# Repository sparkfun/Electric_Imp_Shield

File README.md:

Electric Imp Shield
===================

[
*Electric Imp Shield (DEV-12887)*](https://www.sparkfun.com/products/12887)

The Electric Imp shield allows you to connect your Arduino to the Imp Cloud Service and connect to HTTP APIs. 

Repository Contents
-------------------
* **/Hardware** - All Eagle design files (.brd, .sch)
* **/Production** - Test bed files and production panel files

Product Versions
----------------
* [DEV-11401](https://www.sparkfun.com/products/retired/11401)- Version 1.1. Designed for Uno (not R3). Retired. 

Version History
---------------
* [v1.1](https://github.com/sparkfun/Electric_Imp_Shield/tree/V_1.1) Version 1.1

License Information
-------------------
The hardware is released under [Creative Commons ShareAlike 4.0 International](https://creativecommons.org/licenses/by-sa/4.0/).The code is beerware; if you see me (or any other SparkFun employee) at the local, and you've found our code helpful, please buy us a round!

Distributed as-is; no warranty is given.

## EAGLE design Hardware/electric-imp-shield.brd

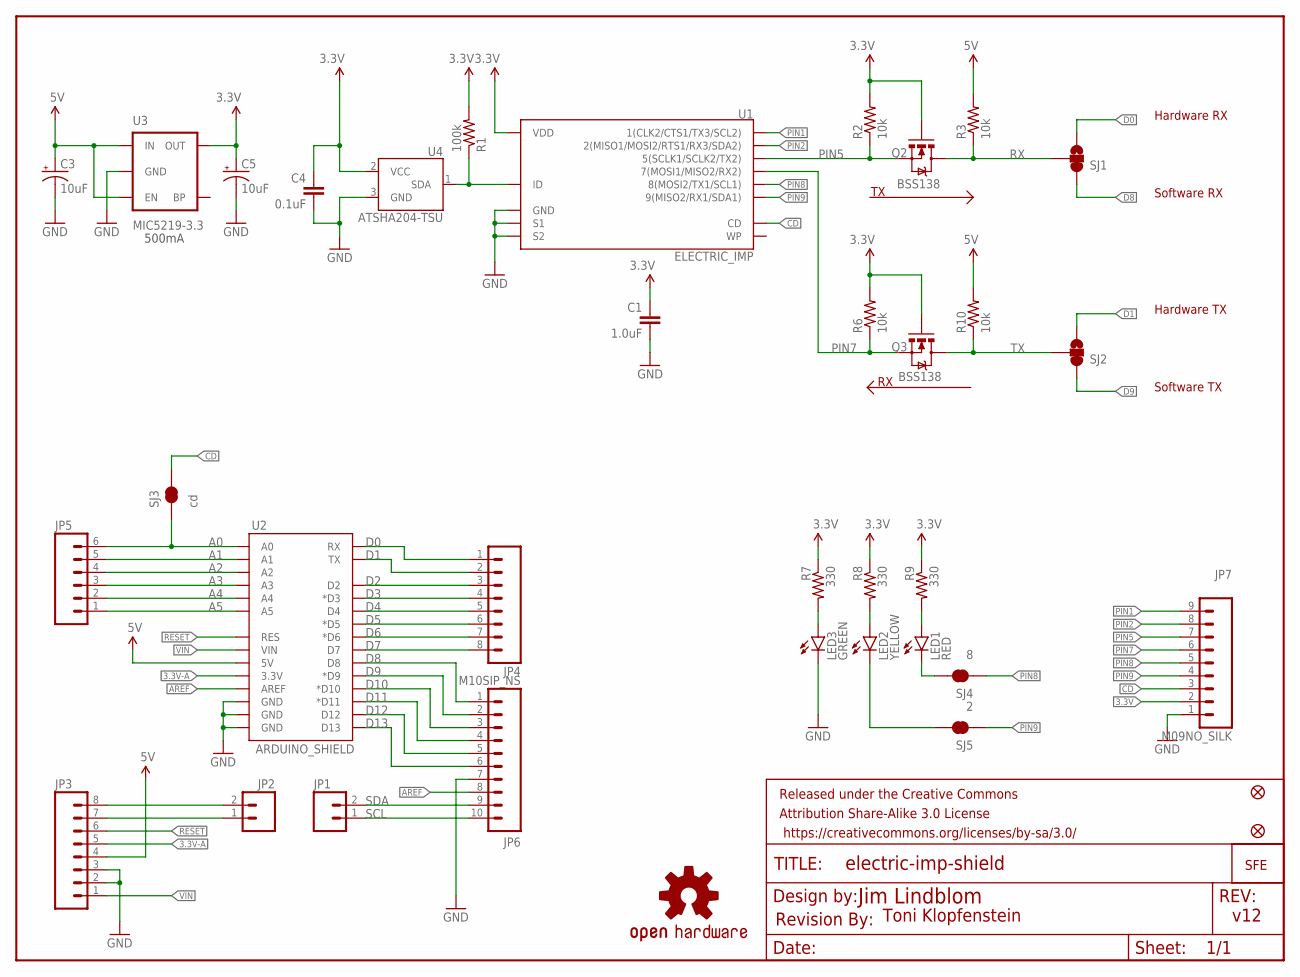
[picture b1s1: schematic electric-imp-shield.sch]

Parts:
C1: 1.0uF; 0603-CAP
C3, C5: 10uF; EIA3216
C4: 0.1uF; 0603-CAP
FID1, FID2: FIDUCIAL1X2; FIDUCIAL-1X2
FRAME1: FRAME-LETTER; CREATIVE_COMMONS
JP1, JP2: M021X02_NO_SILK; 1X02_NO_SILK
JP3, JP4: M08SIP_NS; 1X08_NO_SILK
JP5: M06SIP_NS; 1X06_NO_SILK
JP6: M10SIP_NS; 1X10_NO_SILK
JP7: M09NO_SILK; 1X09_NO_SILK
JP10: LOGO-SFENW2; SFE-NEW-WEB
LED1: RED; LED-0603
LED2: YELLOW; LED-0603
LED3: GREEN; LED-0603
Q2, Q3: BSS138; SOT23-3
R1: 100k; 0603-RES
R2, R3, R6, R10: 10k; 0603-RES
R7, R8, R9: 330; 0603-RES
SJ1, SJ2: SOLDERJUMPER_2WAYS; SJ_3
SJ3: cd; SJ_2S-TRACE
SJ4: 8; SJ_2S-TRACE
SJ5: 2; SJ_2S-TRACE
U1: ELECTRIC_IMP; SD_1:1
U2: ARDUINO_SHIELD; DUEMILANOVE_SHIELD_NOHOLES_NOLABELS
U3: MIC5219-3.3; SOT23-5
U4: ATSHA204-TSU; SOT23-3
U$6: REVISION
U$7: OSHW-LOGOS; OSHW-LOGO-S

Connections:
3.3V: C1.1, C4.1, C5.A (+), JP7.2, Q2.1 (G), Q3.1 (G), R1.2, R2.2, R6.2, R7.1, R8.1, R9.1, U1.4 (VDD), U3.5 (OUT), U4.2 (VCC)
3.3V-A: JP3.5, U2.3.3V
5V: C3.A (+), JP3.4, R3.2, R10.2, U2.5V, U3.1 (IN), U3.3 (EN)
A0: JP5.6, SJ3.1, U2.A0
A1: JP5.5, U2.A1
A2: JP5.4, U2.A2
A3: JP5.3, U2.A3
A4: JP5.2, U2.A4
A5: JP5.1, U2.A5
ACTIVITY: LED1.C, SJ4.2
AREF: JP6.8, U2.AREF
CD: JP7.3, SJ3.2, U1.CD
D0: JP4.1, SJ1.3, U2.RX
D1: JP4.2, SJ2.3, U2.TX
D2: JP4.3, U2.D2
D3: JP4.4, U2.D3 (*D3)
D4: JP4.5, U2.D4
D5: JP4.6, U2.D5 (*D5)
D6: JP4.7, U2.D6 (*D6)
D7: JP4.8, U2.D7
D8: JP6.1, SJ1.1, U2.D8
D9: JP6.2, SJ2.1, U2.D9 (*D9)
D10: JP6.3, U2.D10 (*D10)
D11: JP6.4, U2.D11 (*D11)
D12: JP6.5, U2.D12
D13: JP6.6, U2.D13
GND: C1.2, C3.C (-), C4.2, C5.C (-), JP3.2, JP3.3, JP6.7, JP7.1, LED3.C, U1.3 (GND), U1.SH@1 (S1), U1.SH@2 (S2), U2.GND@0 (GND), U2.GND@1 (GND), U2.GND@2 (GND), U3.2 (GND), U4.3 (GND)
LINK: LED2.C, SJ5.2
unnamed: R1.1, U1.6 (ID), U4.1 (SDA)
unnamed: JP2.2, JP3.8
unnamed: JP2.1, JP3.7
unnamed: LED3.A, R7.2
unnamed: LED2.A, R8.2
unnamed: LED1.A, R9.2
PIN1: JP7.9, U1.1 (1(CLK2/CTS1/TX3/SCL2))
PIN2: JP7.8, U1.2 (2(MISO1/MOSI2/RTS1/RX3/SDA2))
PIN5: JP7.7, Q2.2 (S), R2.1, U1.5 (5(SCLK1/SCLK2/TX2))
PIN7: JP7.6, Q3.2 (S), R6.1, U1.7 (7(MOSI1/MISO2/RX2))
PIN8: JP7.5, SJ4.1, U1.8 (8(MOSI2/TX1/SCL1))
PIN9: JP7.4, SJ5.1, U1.9 (9(MISO2/RX1/SDA1))
RESET: JP3.6, U2.RES
RX: Q2.3 (D), R3.1, SJ1.2
SCL: JP1.1, JP6.10
SDA: JP1.2, JP6.9
TX: Q3.3 (D), R10.1, SJ2.2
VIN: JP3.1, U2.VIN

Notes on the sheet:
Hardware RX
Software RX
Hardware TX
Software TX
500mA
Jim Lindblom
v12
Toni Klopfenstein

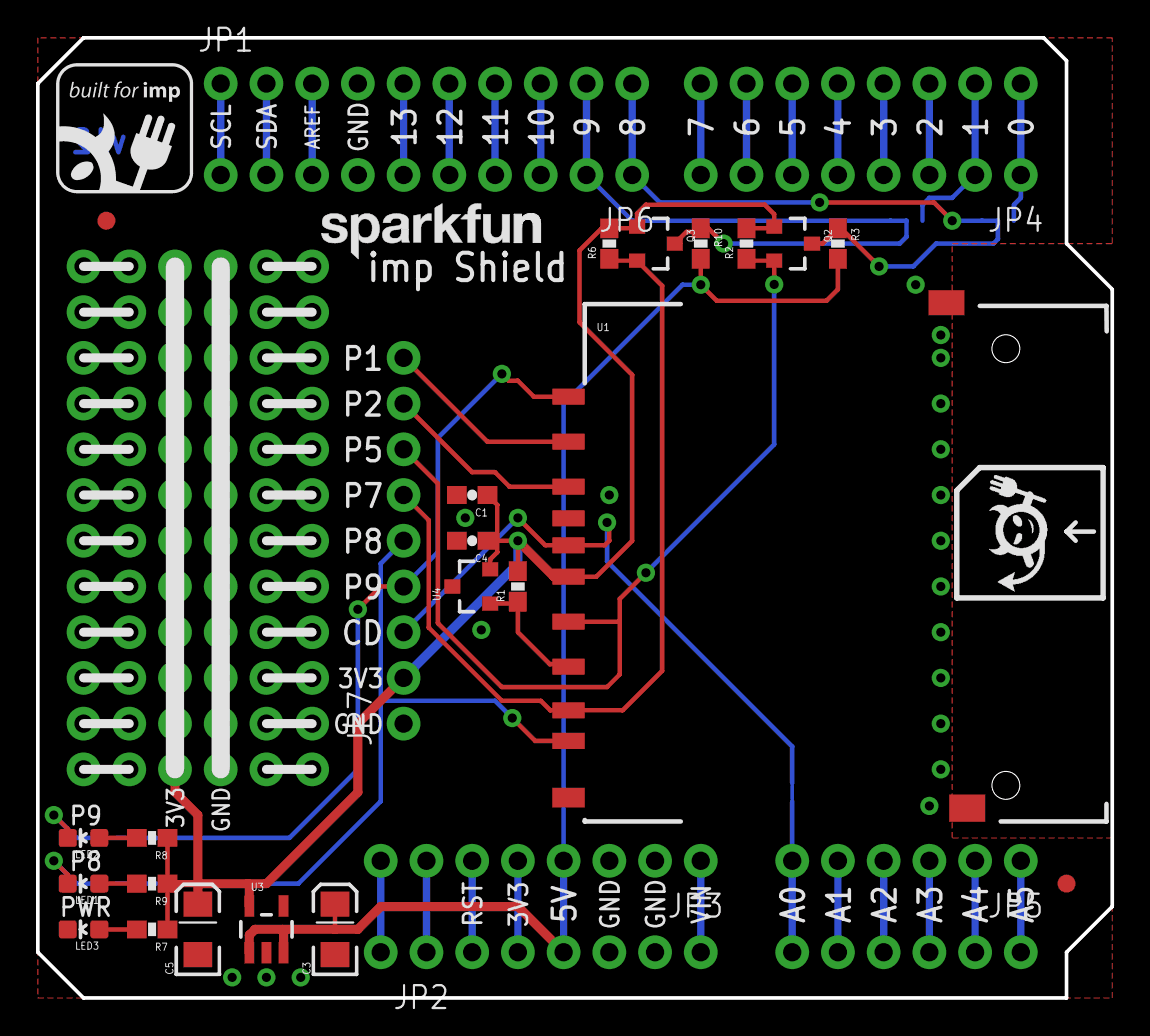
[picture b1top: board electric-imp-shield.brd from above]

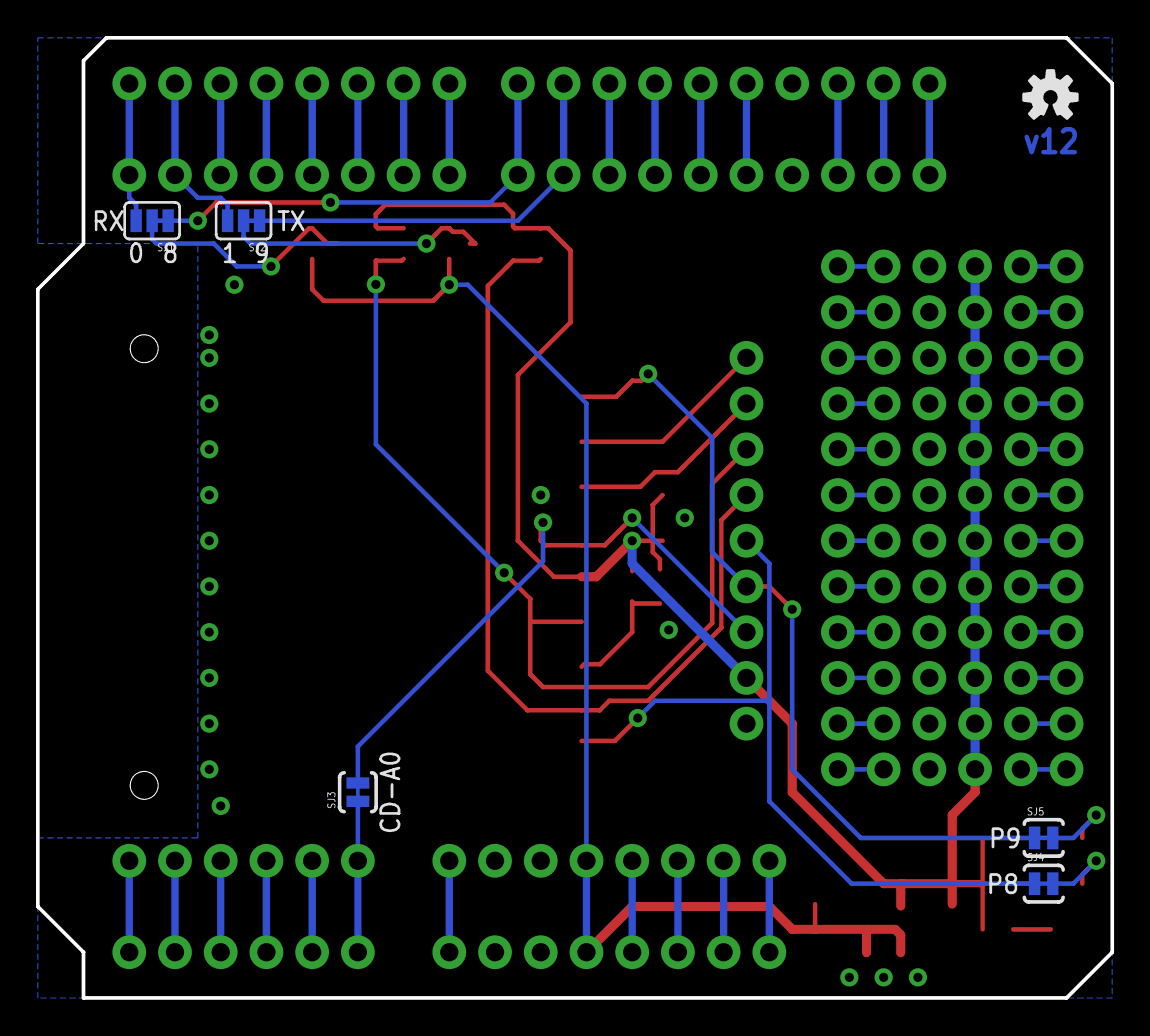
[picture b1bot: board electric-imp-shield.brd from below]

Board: 2 copper layers, 59.7 x 53.3 mm, 39 parts (6 on the bottom side), 46 nets.

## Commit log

2014-07-03 Adding readme and hardware files
2014-07-03 Update README.md
    Adding in product image and links.
2014-07-03 Updating to new socket fp, 0603 packages, schematic updates
2014-07-07 Fixing airwire
2014-08-06 removed micro fids, added regulars
2014-08-06 Fixing copper version number
2014-08-06 created panel v12
2014-10-17 Updating README with new product links

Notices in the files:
parts and their libraries:
SparkFun-Boards: Licensing: CC v3.0 Share-Alike You are welcome to use this library for commercial purposes.
SparkFun-Resistors: Licensing: Creative Commons ShareAlike 4.0 International - https://creativecommons.org/licenses/by-sa/4.0
SparkFun-Retired: https://creativecommons.org/licenses/by-sa/3.0
